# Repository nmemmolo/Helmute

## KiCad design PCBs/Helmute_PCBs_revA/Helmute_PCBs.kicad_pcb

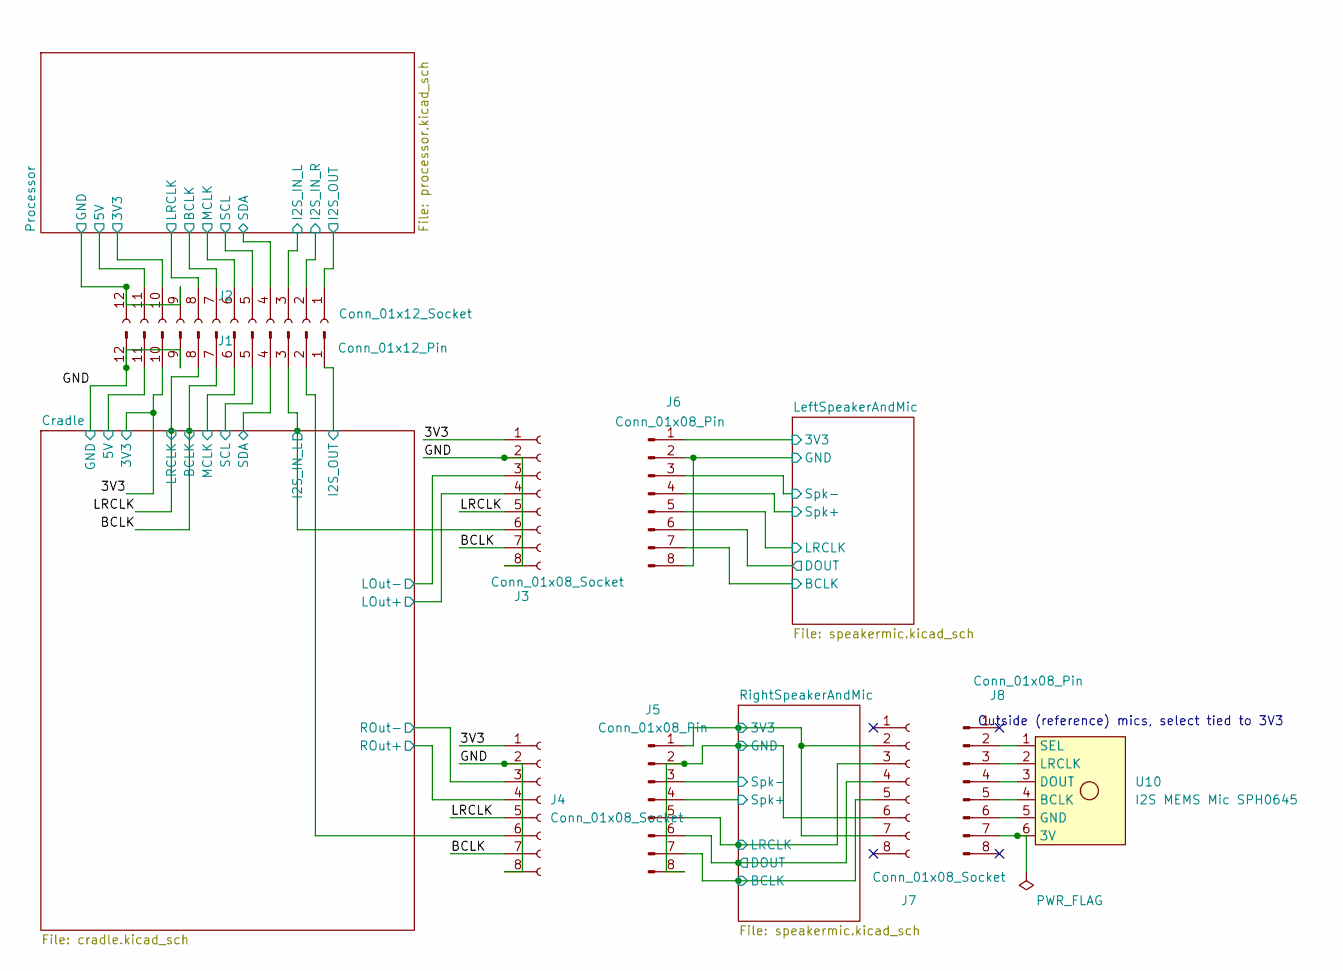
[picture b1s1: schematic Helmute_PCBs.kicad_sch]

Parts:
J1: Conn_01x12_Socket; PinHeader_2x06_P2.54mm_Vertical
J2: Conn_01x12_Pin; PinHeader_2x06_P2.54mm_Vertical
J3, J4, J7: Conn_01x08_Socket; JST_XH_S8B-XH-A_1x08_P2.50mm_Horizontal
J5, J6, J8: Conn_01x08_Pin; JST_XH_S8B-XH-A_1x08_P2.50mm_Horizontal
U10: I2S MEMS Mic SPH0645; I2S SPK0415HM4H

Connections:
/3V3: J2.10, J3.1, J4.1; also elsewhere on the board
/BCLK: J2.7, J3.7, J4.7; also elsewhere on the board
/Cradle/5V_CRD: J2.11; also elsewhere on the board
/Cradle/I2S_IN_L: J2.3, J3.6; also elsewhere on the board
/Cradle/I2S_OUT1: J2.1; also elsewhere on the board
/Cradle/LOut+: J3.4; also elsewhere on the board
/Cradle/LOut-: J3.3; also elsewhere on the board
/Cradle/MCLK1: J2.6; also elsewhere on the board
/Cradle/ROut+: J4.4; also elsewhere on the board
/Cradle/ROut-: J4.3; also elsewhere on the board
/Cradle/SCL: J2.5; also elsewhere on the board
/Cradle/SDA: J2.4; also elsewhere on the board
/GND: J2.9, J2.12, J3.2, J3.8, J4.2, J4.8; also elsewhere on the board
/LRCLK: J2.8, J3.5, J4.5; also elsewhere on the board
/Processor/3V3: J1.10; also elsewhere on the board
/Processor/5V_MCU: J1.11; also elsewhere on the board
/Processor/GND_MCU: J1.9, J1.12; also elsewhere on the board
/Processor/I2S_BCLK: J1.7; also elsewhere on the board
/Processor/I2S_IN_L: J1.3; also elsewhere on the board
/Processor/I2S_IN_R: J1.2; also elsewhere on the board
/Processor/I2S_LRCLK: J1.8; also elsewhere on the board
/Processor/I2S_OUT: J1.1; also elsewhere on the board
/Processor/MCLK: J1.6; also elsewhere on the board
/Processor/SCL: J1.5; also elsewhere on the board
/Processor/SDA: J1.4; also elsewhere on the board
/RightSpeakerAndMic/3V3_SPK: J5.1, J7.2, J7.7; also elsewhere on the board
/RightSpeakerAndMic/BCLK: J5.7, J7.5; also elsewhere on the board
/RightSpeakerAndMic/DOUT: J5.6, J7.4; also elsewhere on the board
/RightSpeakerAndMic/GND_SPK: J5.2, J5.8, J7.6; also elsewhere on the board
/RightSpeakerAndMic/LRCLK: J5.5, J7.3; also elsewhere on the board
/RightSpeakerAndMic/Spk+: J5.4; also elsewhere on the board
/RightSpeakerAndMic/Spk-: J5.3; also elsewhere on the board
unnamed: J2.2, J4.6
unnamed: J6.2, J6.8
unnamed: J8.2, U10.1 (SEL)
unnamed: J8.3, U10.2 (LRCLK)
unnamed: J8.4, U10.3 (DOUT)
unnamed: J8.5, U10.4 (BCLK)
unnamed: J8.6, U10.5 (GND)
unnamed: J8.7, U10.6 (3V)

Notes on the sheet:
Outside (reference) mics, select tied to 3V3

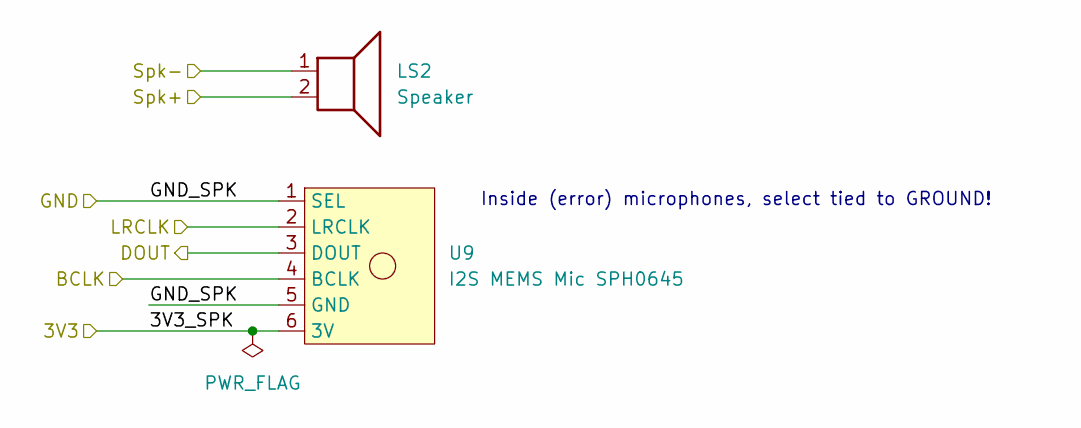
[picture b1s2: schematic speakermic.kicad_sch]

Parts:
LS2: Speaker; SpeakerConnections
U9: I2S MEMS Mic SPH0645; I2S SPK0415HM4H

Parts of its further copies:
LS1: Speaker; SpeakerConnections
U8: I2S MEMS Mic SPH0645; I2S SPK0415HM4H

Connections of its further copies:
/RightSpeakerAndMic/3V3_SPK: U8.6 (3V); also elsewhere on the board
/RightSpeakerAndMic/BCLK: U8.4 (BCLK); also elsewhere on the board
/RightSpeakerAndMic/DOUT: U8.3 (DOUT); also elsewhere on the board
/RightSpeakerAndMic/GND_SPK: U8.1 (SEL), U8.5 (GND); also elsewhere on the board
/RightSpeakerAndMic/LRCLK: U8.2 (LRCLK); also elsewhere on the board
/RightSpeakerAndMic/Spk+: LS1.2; also elsewhere on the board
/RightSpeakerAndMic/Spk-: LS1.1; also elsewhere on the board

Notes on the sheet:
Inside (error) microphones, select tied to GROUND!

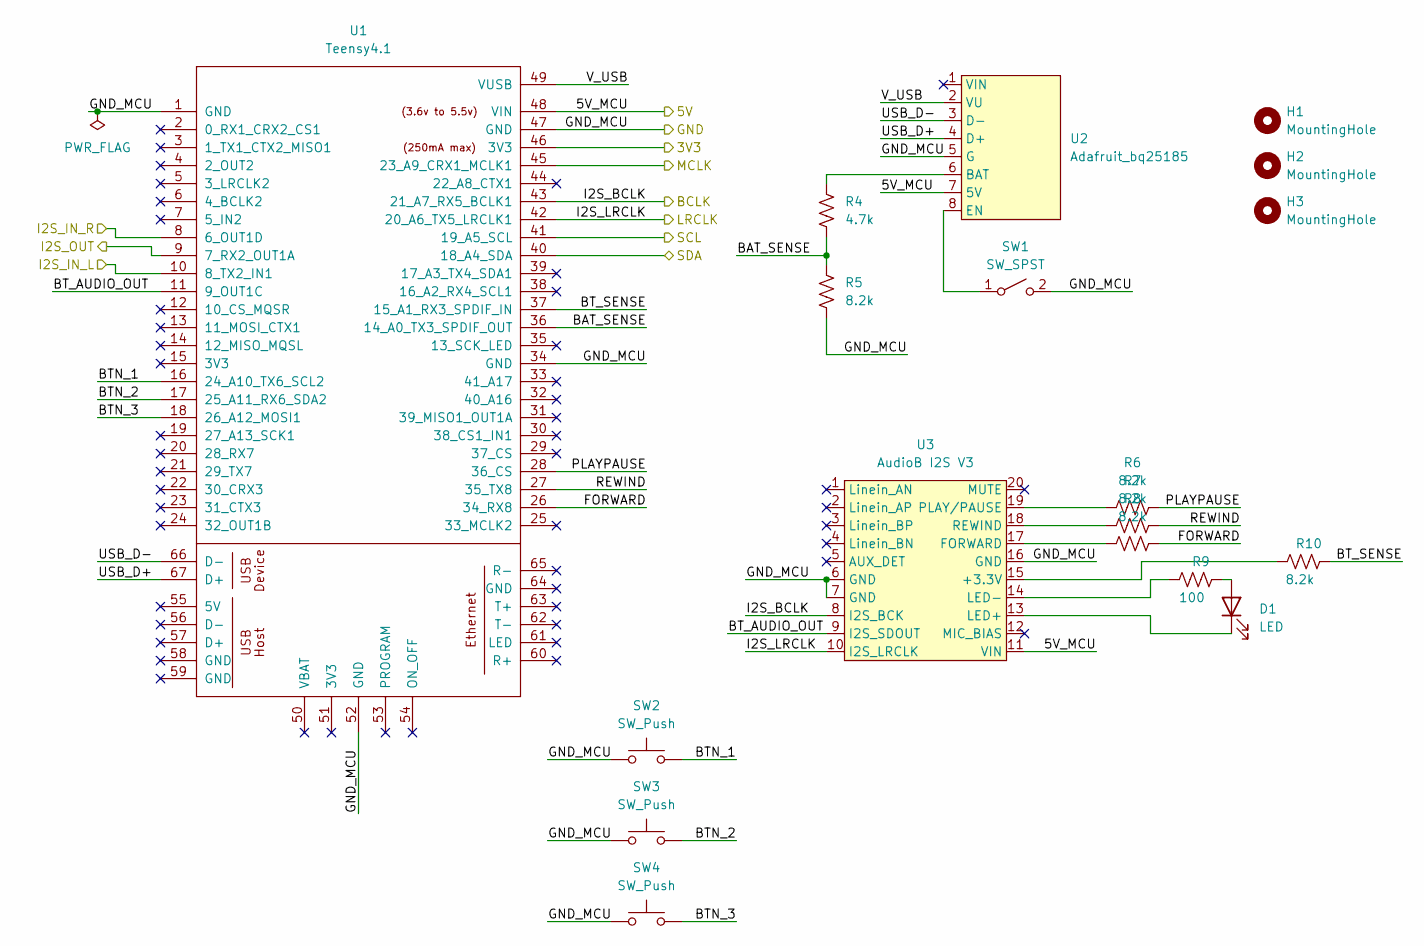
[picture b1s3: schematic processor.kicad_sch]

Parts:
D1: LED; LED_D5.0mm
H1, H2, H3: MountingHole; MountingHole_3.2mm_M3
R4: 4.7k; R_0805_2012Metric
R5, R6, R7, R8, R10: 8.2k; R_0805_2012Metric
R9: 100; R_0805_2012Metric
SW1: SW_SPST; SW_Slide_SPDT_Angled_CK_OS102011MA1Q
SW2, SW3, SW4: SW_Push; SW_PUSH_6mm
U1: Teensy4.1; Teensy41
U2: Adafruit_bq25185; bq25185 5V Boost Breakout
U3: AudioB I2S V3; AudioB

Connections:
/Processor/3V3: U1.46 (3V3); also elsewhere on the board
/Processor/5V_MCU: U1.48 (VIN), U2.7 (5V), U3.11 (VIN); also elsewhere on the board
/Processor/BAT_SENSE: R4.2, R5.1, U1.36 (14_A0_TX3_SPDIF_OUT)
/Processor/BTN_1: SW2.2, U1.16 (24_A10_TX6_SCL2)
/Processor/BTN_2: SW3.2, U1.17 (25_A11_RX6_SDA2)
/Processor/BTN_3: SW4.2, U1.18 (26_A12_MOSI1)
/Processor/BT_AUDIO_OUT: U1.11 (9_OUT1C), U3.9 (I2S_SDOUT)
/Processor/BT_SENSE: R10.2, U1.37 (15_A1_RX3_SPDIF_IN)
/Processor/FORWARD: R8.2, U1.26 (34_RX8)
/Processor/GND_MCU: R5.2, SW1.2 (B), SW2.1, SW3.1, SW4.1, U1.1 (GND), U1.34 (GND), U1.47 (GND), U1.52 (GND), U2.5 (G), U3.6 (GND), U3.7 (GND), U3.16 (GND); also elsewhere on the board
/Processor/I2S_BCLK: U1.43 (21_A7_RX5_BCLK1), U3.8 (I2S_BCK); also elsewhere on the board
/Processor/I2S_IN_L: U1.10 (8_TX2_IN1); also elsewhere on the board
/Processor/I2S_IN_R: U1.8 (6_OUT1D); also elsewhere on the board
/Processor/I2S_LRCLK: U1.42 (20_A6_TX5_LRCLK1), U3.10 (I2S_LRCLK); also elsewhere on the board
/Processor/I2S_OUT: U1.9 (7_RX2_OUT1A); also elsewhere on the board
/Processor/MCLK: U1.45 (23_A9_CRX1_MCLK1); also elsewhere on the board
/Processor/PLAYPAUSE: R6.2, U1.28 (36_CS)
/Processor/REWIND: R7.2, U1.27 (35_TX8)
/Processor/SCL: U1.41 (19_A5_SCL); also elsewhere on the board
/Processor/SDA: U1.40 (18_A4_SDA); also elsewhere on the board
/Processor/USB_D+: U1.67 (D+), U2.4 (D+)
/Processor/USB_D-: U1.66 (D-), U2.3 (D-)
/Processor/V_USB: U1.49 (VUSB), U2.2 (VU)
unnamed: D1.2 (A), R9.2
unnamed: D1.1 (K), U3.13 (LED+)
unnamed: SW1.1 (A), U2.8 (EN)
unnamed: R4.1, U2.6 (BAT)
unnamed: R10.1, U3.15 (+3.3V)
unnamed: R8.1, U3.17 (FORWARD)
unnamed: R9.1, U3.14 (LED-)
unnamed: R6.1, U3.19 (PLAY/PAUSE)
unnamed: R7.1, U3.18 (REWIND)

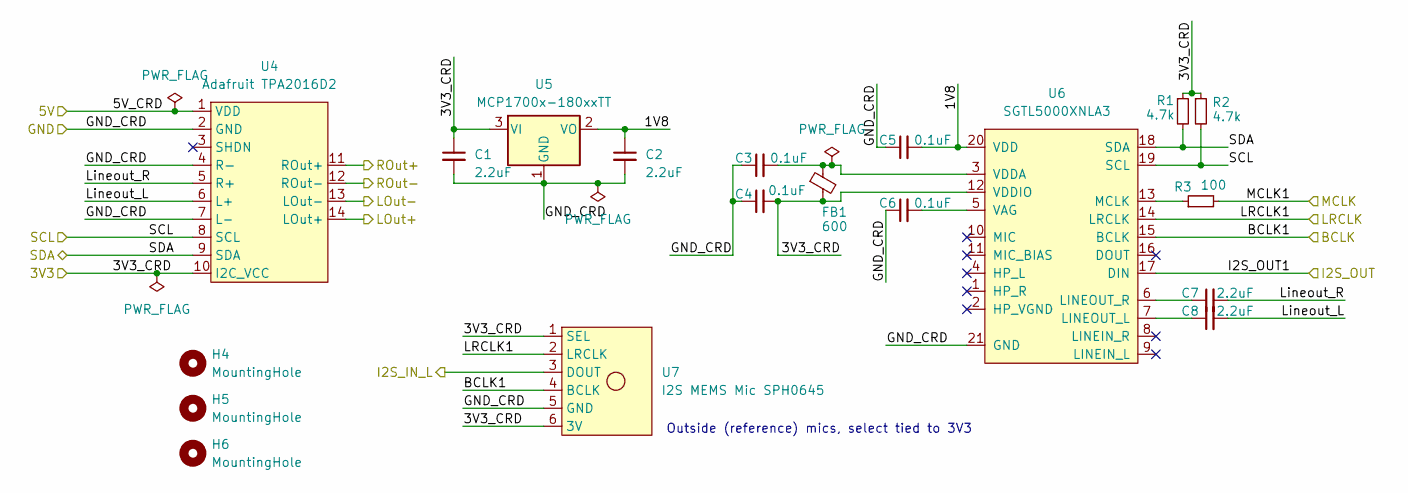
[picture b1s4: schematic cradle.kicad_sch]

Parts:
C1, C2, C7, C8: 2.2uF; C_0805_2012Metric
C3, C4, C5, C6: 0.1uF; C_0805_2012Metric
FB1: 600; C_0805_2012Metric
H4, H5, H6: MountingHole; MountingHole_3.2mm_M3
R1, R2: 4.7k; R_0805_2012Metric
R3: 100; R_0805_2012Metric
U4: Adafruit TPA2016D2; TPA22016D2new
U5: MCP1700x-180xxTT; SOT-23
U6: SGTL5000XNLA3; QFN-20-1EP_3x3mm_P0.4mm_EP1.65x1.65mm
U7: I2S MEMS Mic SPH0645; I2S SPK0415HM4H

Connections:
/3V3: C1.1, C4.2, FB1.2, R1.1, R2.1, U4.10 (I2C_VCC), U5.3 (VI), U6.12 (VDDIO), U7.1 (SEL), U7.6 (3V); also elsewhere on the board
/BCLK: U6.15 (BCLK), U7.4 (BCLK); also elsewhere on the board
/Cradle/1V8: C2.1, C5.2, U5.2 (VO), U6.20 (VDD)
/Cradle/5V_CRD: U4.1 (VDD); also elsewhere on the board
/Cradle/I2S_IN_L: U7.3 (DOUT); also elsewhere on the board
/Cradle/I2S_OUT1: U6.17 (DIN); also elsewhere on the board
/Cradle/LOut+: U4.14 (LOut+); also elsewhere on the board
/Cradle/LOut-: U4.13 (LOut-); also elsewhere on the board
/Cradle/Lineout_L: C8.2, U4.6 (L+)
/Cradle/Lineout_R: C7.2, U4.5 (R+)
/Cradle/MCLK1: R3.2; also elsewhere on the board
/Cradle/ROut+: U4.11 (ROut+); also elsewhere on the board
/Cradle/ROut-: U4.12 (ROut-); also elsewhere on the board
/Cradle/SCL: R2.2, U4.8 (SCL), U6.19 (SCL); also elsewhere on the board
/Cradle/SDA: R1.2, U4.9 (SDA), U6.18 (SDA); also elsewhere on the board
/GND: C1.2, C2.2, C3.1, C4.1, C5.1, C6.1, U4.2 (GND), U4.4 (R-), U4.7 (L-), U5.1 (GND), U6.21 (GND), U7.5 (GND); also elsewhere on the board
/LRCLK: U6.14 (LRCLK), U7.2 (LRCLK); also elsewhere on the board
unnamed: C8.1, U6.7 (LINEOUT_L)
unnamed: C7.1, U6.6 (LINEOUT_R)
unnamed: R3.1, U6.13 (MCLK)
unnamed: C6.2, U6.5 (VAG)
unnamed: C3.2, FB1.1, U6.3 (VDDA)

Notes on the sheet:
Outside (reference) mics, select tied to 3V3

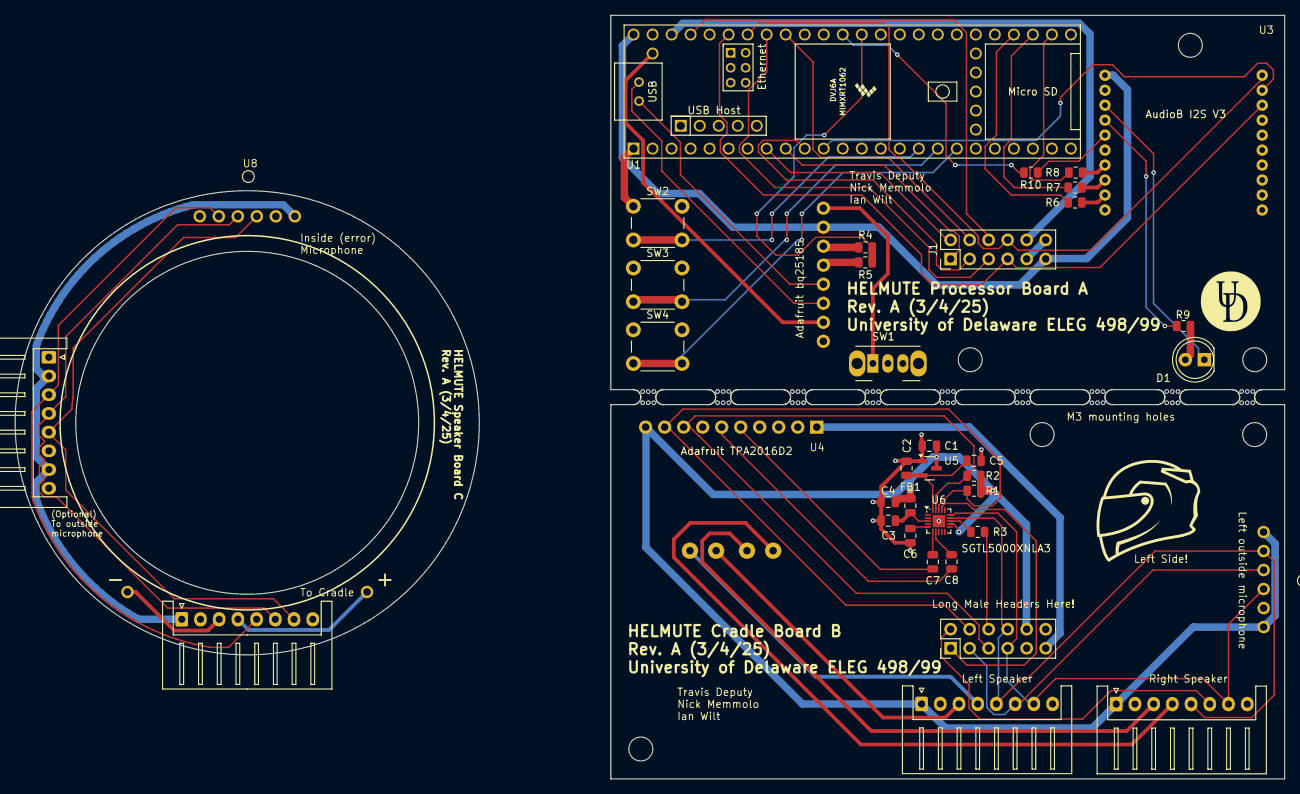
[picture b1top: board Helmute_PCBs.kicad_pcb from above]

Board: 2 copper layers, 169.6 x 102.0 mm, 56 parts (0 on the bottom side), 62 nets.

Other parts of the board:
B1, B2: Board
mouse-bite-2mm-slot, mouse-bite-2mm-slot1, mouse-bite-2mm-slot2, mouse-bite-2mm-slot3, mouse-bite-2mm-slot4, mouse-bite-2mm-slot5, mouse-bite-2mm-slot6, mouse-bite-2mm-slot7, mouse-bite-2mm-slot8: VAL**; mouse-bite-2mm-slot

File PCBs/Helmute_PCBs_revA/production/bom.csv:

Designator,Footprint,Quantity,Value,LCSC Part #
"C1, C2, C7, C8",0805,4,2.2uF,
"C3, C4, C5, C6",0805,4,0.1uF,
D1,LED_D5.0mm,1,LED,
FB1,0805,1,600,
J1,PinHeader_2x06_P2.54mm_Vertical,1,Conn_01x12_Socket,
J2,PinHeader_2x06_P2.54mm_Vertical,1,Conn_01x12_Pin,
"J3, J4, J7",JST_XH_S8B-XH-A_1x08_P2.50mm_Horizontal,3,Conn_01x08_Socket,
J5,JST_XH_S8B-XH-A_1x08_P2.50mm_Horizontal,1,Conn_01x08_Pin,
LS1,SpeakerConnections,1,Speaker,
"MOUSE-BITE-2MM-SLOT, MOUSE-BITE-2MM-SLOT1, MOUSE-BITE-2MM-SLOT2, MOUSE-BITE-2MM-SLOT3, MOUSE-BITE-2MM-SLOT4, MOUSE-BITE-2MM-SLOT5, MOUSE-BITE-2MM-SLOT6, MOUSE-BITE-2MM-SLOT7, MOUSE-BITE-2MM-SLOT8",mouse-bite-2mm-slot,9,VAL**,
"R1, R2, R4",0805,3,4.7k,
"R10, R5, R6, R7, R8",0805,5,8.2k,
"R3, R9",0805,2,100,
SW1,SW_Slide_SPDT_Angled_CK_OS102011MA1Q,1,SW_SPST,
"SW2, SW3, SW4",SW_PUSH_6mm,3,SW_Push,
U1,Teensy41,1,Teensy4.1,
U2,bq25185 5V Boost Breakout,1,Adafruit bq25185,
U3,AudioB,1,AudioB I2S V3,
U4,TPA22016D2new,1,Adafruit TPA2016D2,
U5,SOT-23,1,MCP1700x-180xxTT,
U6,QFN-20-1EP_3x3mm_P0.4mm_EP1.65x1.65mm,1,SGTL5000XNLA3,
"U7, U8",I2S SPK0415HM4H,2,I2S MEMS Mic SPH0645,

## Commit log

2025-03-11 Create PCB Files
    storage space for custom PCB files
2025-03-11 Add things I worked on
    My code and PCB documents
2025-05-15 Create 3D Models
2025-05-15 Create Print Files
